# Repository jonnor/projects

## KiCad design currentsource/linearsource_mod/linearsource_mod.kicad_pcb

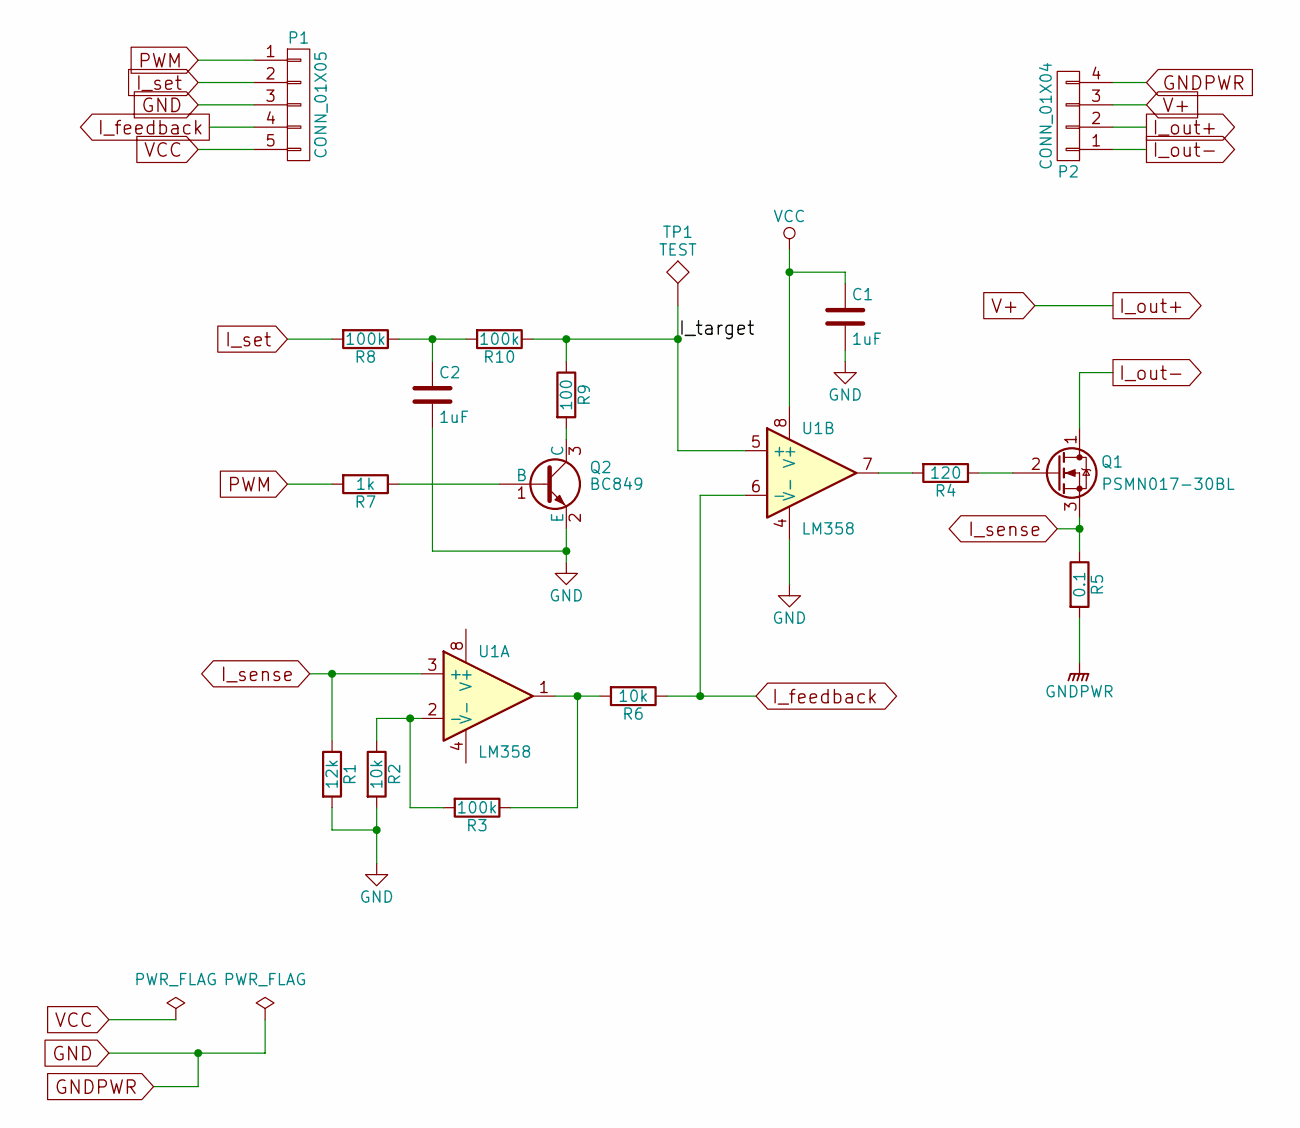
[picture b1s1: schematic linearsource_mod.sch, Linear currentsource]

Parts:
C1, C2: 1uF; C_1206
P1: CONN_01X05; Pin_Header_Edge_1x05_Pitch2.54mm
P2: CONN_01X04
Q1: PSMN017-30BL; TO-263-3Lead
Q2: BC849; SOT-323
R1: 12k; R_1206
R2, R6: 10k; R_1206
R3, R8, R10: 100k; R_1206
R4: 120; R_1206
R5: 0.1; R_2512
R7: 1k; R_1206
R9: 100; R_1206
TP1: TEST; 1Pin
U1: LM358; SOIC-8-N

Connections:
/I_target: R9.1, R10.1, TP1.1, U1.5 (+)
GND: C1.2, C2.2, P1.3, P2.4, Q2.2 (E), R1.2, R2.2, R5.2, U1.4 (V-)
I_feedback: P1.4, R6.1, U1.6 (-)
I_out+: P2.2, P2.3
I_out-: P2.1, Q1.1 (D)
I_sense: Q1.3 (S), R1.1, R5.1, U1.3 (+)
I_set: P1.2, R8.2
unnamed: C2.1, R8.1, R10.2
unnamed: Q1.2 (G), R4.1
unnamed: Q2.1 (B), R7.1
unnamed: Q2.3 (C), R9.2
unnamed: R2.1, R3.2, U1.2 (-)
unnamed: R3.1, R6.2, U1.1
unnamed: R4.2, U1.7
PWM: P1.1, R7.2
VCC: C1.1, P1.5, U1.8 (V+)

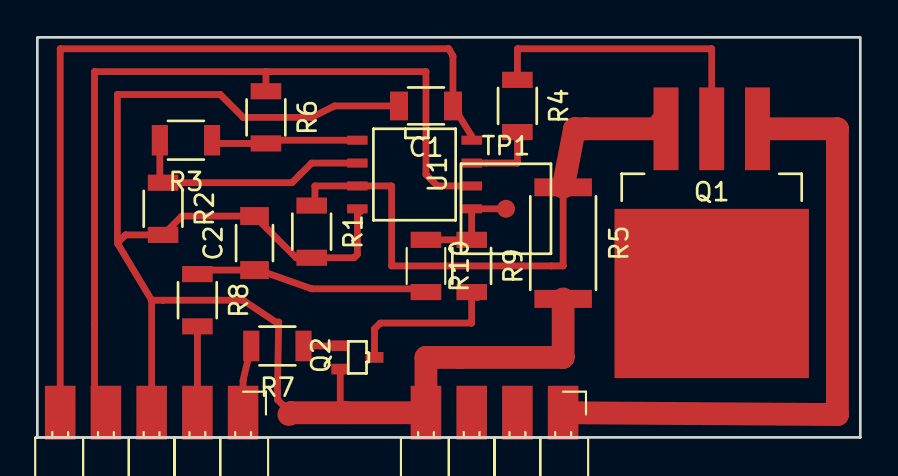
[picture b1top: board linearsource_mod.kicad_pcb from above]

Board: 2 copper layers, 45.7 x 22.2 mm, 18 parts (0 on the bottom side), 16 nets.

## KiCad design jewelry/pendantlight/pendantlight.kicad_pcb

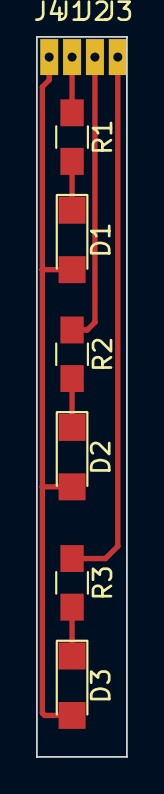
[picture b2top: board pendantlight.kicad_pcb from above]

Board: 2 copper layers, 5.0 x 40.0 mm, 10 parts (0 on the bottom side), 7 nets.

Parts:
D1, D2, D3: LED; LED_1206
J1, J2, J3, J4: Conn_01x01; SolderWirePad_single_0-8mmDrill
R1, R2, R3: 47R; R_0805_HandSoldering

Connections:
unnamed: D1.1, R1.2
unnamed: D1.2, D2.2, D3.2, J4.1
unnamed: D2.1, R2.2
unnamed: D3.1, R3.2
unnamed: J1.1, R1.1
unnamed: J2.1, R2.1
unnamed: J3.1, R3.1

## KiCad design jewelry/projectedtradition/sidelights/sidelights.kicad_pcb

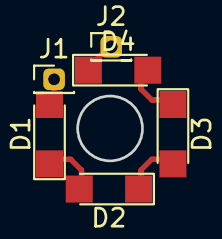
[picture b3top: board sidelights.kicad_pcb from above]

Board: 2 copper layers, 6 parts (0 on the bottom side), 5 nets.

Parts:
D1, D2, D3, D4: LED; LED_1206
J1, J2: Conn_01x01; Pin_Header_Straight_1x01_Pitch1.27mm

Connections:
unnamed: D1.1, D2.2
unnamed: D1.2, J1.1
unnamed: D2.1, D3.2
unnamed: D3.1, D4.2
unnamed: D4.1, J2.1

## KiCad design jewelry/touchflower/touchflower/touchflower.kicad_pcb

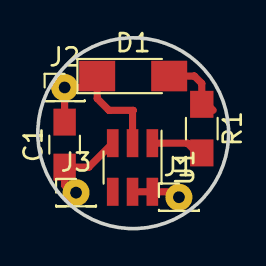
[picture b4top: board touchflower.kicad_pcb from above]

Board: 2 copper layers, 10.6 x 10.6 mm, 7 parts (0 on the bottom side), 5 nets.

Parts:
C1: C; C_0805_HandSoldering
D1: LED; LED_1206_HandSoldering
J1, J2, J3: Conn_01x01; Pin_Header_Straight_1x01_Pitch1.27mm
R1: R; R_0805_HandSoldering
U1: TPP223-BA6; SOT-223-6-extraspace

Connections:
/out: R1.2, U1.1
/sensor: C1.1, J3.1, U1.3
GND: C1.2, D1.1, J2.1, U1.2
unnamed: D1.2, R1.1
VDD: J1.1, U1.5, U1.6

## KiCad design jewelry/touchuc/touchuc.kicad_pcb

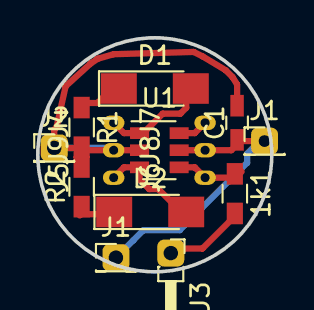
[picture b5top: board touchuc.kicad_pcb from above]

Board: 2 copper layers, 13.0 x 13.0 mm, 17 parts (0 on the bottom side), 9 nets.

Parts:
1k1: R; R_0603_HandSoldering
C1: C; C_0603_HandSoldering
D1, D2: LED; LED_1206_HandSoldering
J1, J1#2, J2: Conn_01x01; Pin_Header_Straight_1x01_Pitch1.27mm
J3: Conn_01x01; Pin_Header_Angled_1x01_Pitch1.27mm
J4, J5, J6, J7, J8, J9: Conn_01x01; progpin
R1, R2: R; R_0603_HandSoldering
U1: ATTINY10-TS; SOT-23-6

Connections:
+BATT: C1.1, J1.1, J1#2.1, J8.1, U1.5
-BATT: C1.2, J2.1, J9.1, R1.2, R2.2, U1.2
/reset: J7.1, U1.6
/sense: 1k1.2, J3.1
LED1: D1.2, J4.1, U1.1
LED2: D2.2, J5.1, U1.3
unnamed: D1.1, R1.1
unnamed: D2.1, R2.1
TOUCH: 1k1.1, J6.1, U1.4

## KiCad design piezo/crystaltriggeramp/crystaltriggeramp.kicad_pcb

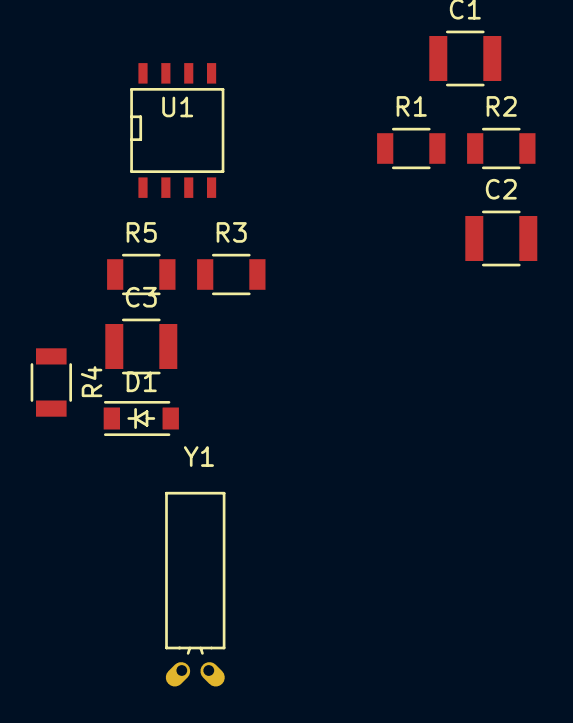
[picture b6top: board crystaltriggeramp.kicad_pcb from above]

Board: 2 copper layers, 11 parts (0 on the bottom side), 8 nets, no tracks yet.

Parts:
C1, C2, C3: C; C_1210
D1: ZENER; SOD-123
R1, R2, R4: 4.7k; R_1206
R3: 10k; R_1206
R5: 47k; R_1206
U1: TL072; SOIC-8-N
Y1: Quarz; Crystal_Round_Horizontal_3mm_BigPad

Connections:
/VGDN: D1.2, R3.2, Y1.2
/VGND: C2.1, R1.2, R2.1
GND: C1.2, C2.2, R2.2, U1.4
unnamed: C3.1, R5.1, U1.1
unnamed: C3.2, R4.1, R5.2, U1.2
unnamed: D1.1, R4.2, Y1.1
unnamed: R3.1, U1.3
VCC: C1.1, R1.1, U1.8

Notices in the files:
currentsource/linearsource_mod/linearsource_mod.sch:
Open Source Hardware under MIT license
